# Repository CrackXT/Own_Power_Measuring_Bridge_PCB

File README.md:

# Own_Power_Measuring_Bridge_PCB

PCB files for Power Measuring Bridge 

# Description

Allows current consumption to be measured directly at the source.

The board can be produced here (AISLER) with the files (.brd and .sch) or by any other PCB manufacturer. -> https://aisler.net/

# Serie

- .dev

# Layout

Top<br>

Bottom<br>

Routing/Dimensions(inch)<br>

Schematic<br>
Schematic as .pdf at the top of the page.

# License

Open hardware, use it, mod it, whatever you want, feel free...

# Thanks!

Own design and layout.

# Version - Build

v1.0 - 06.11.2022

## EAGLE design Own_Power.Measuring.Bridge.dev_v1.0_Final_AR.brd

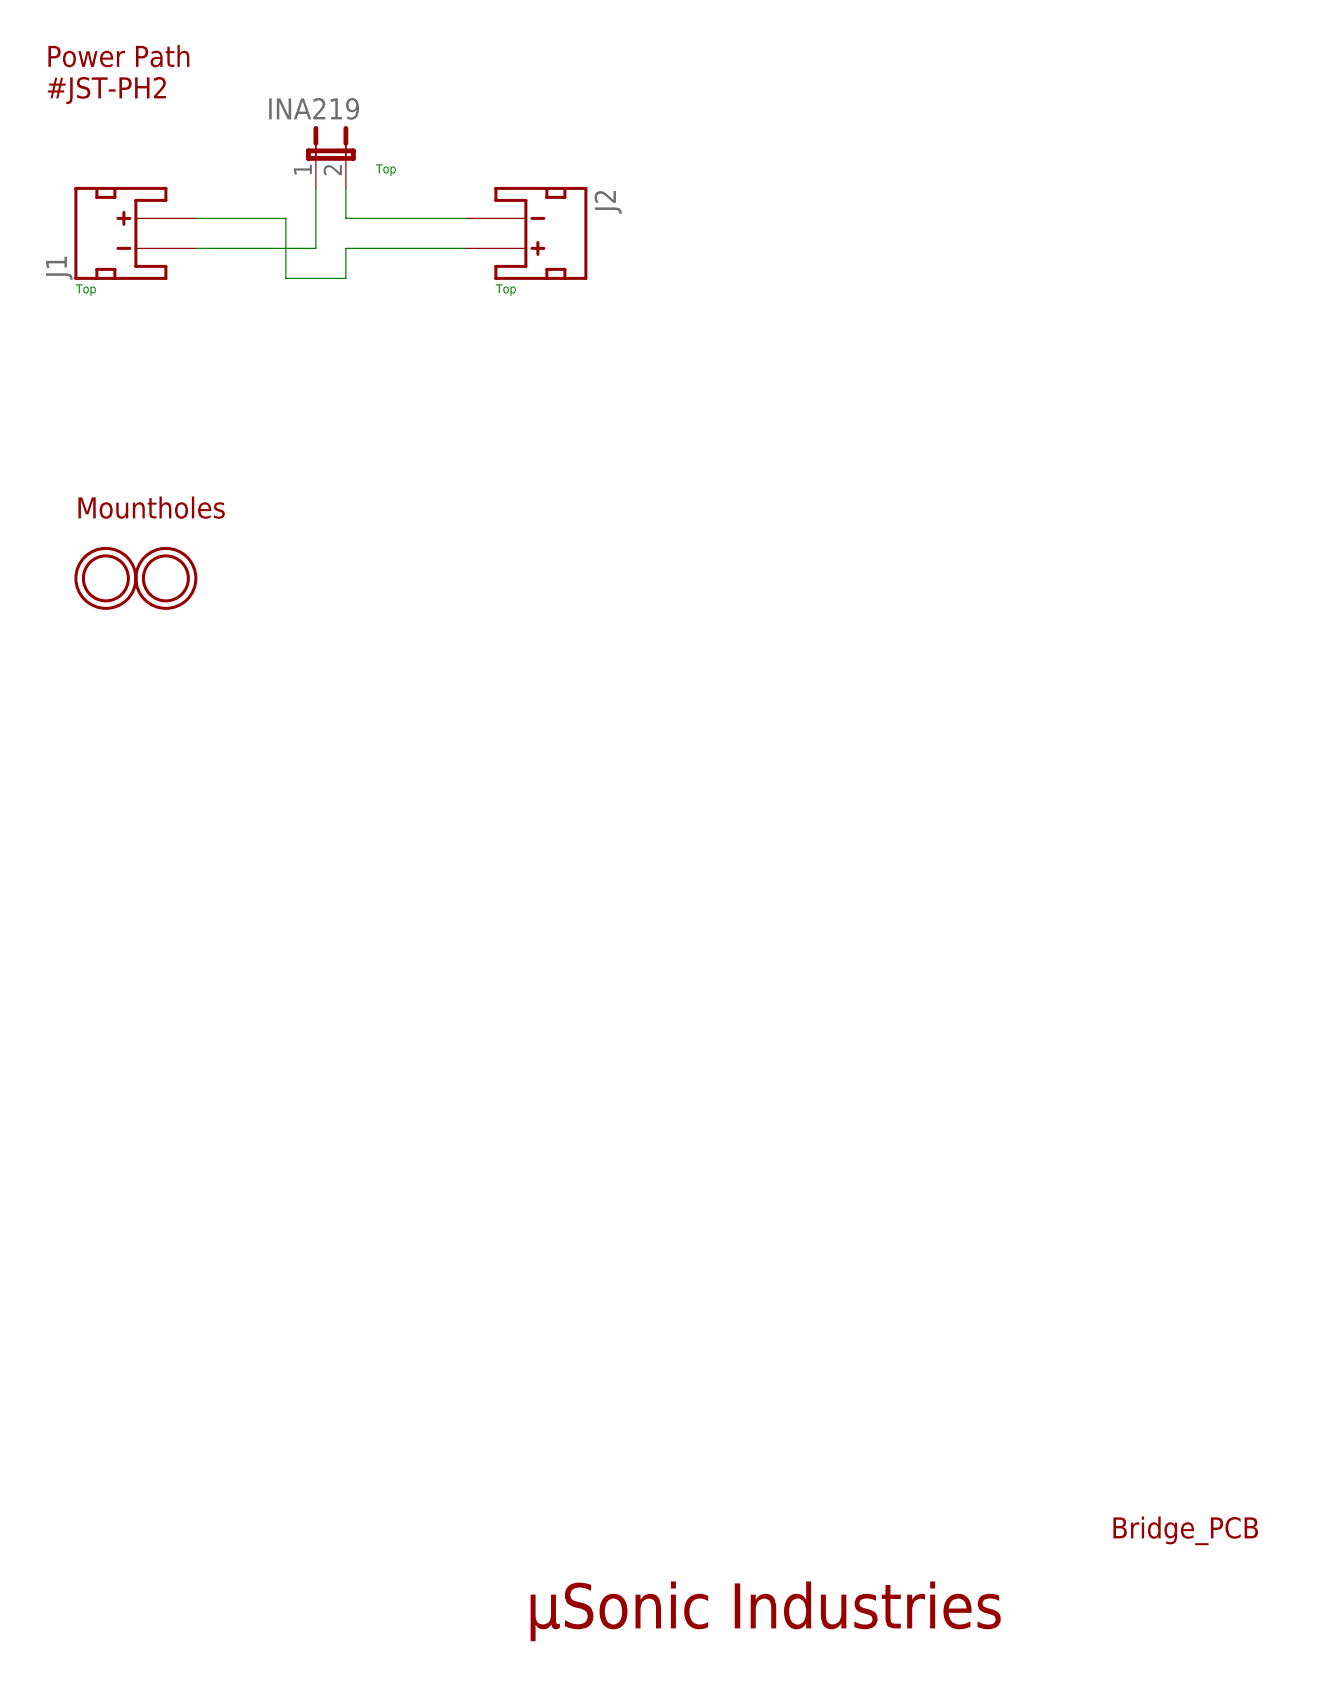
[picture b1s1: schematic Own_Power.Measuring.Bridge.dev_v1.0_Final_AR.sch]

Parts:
INA219: JP1E; JP1
J1: Input; JST-2-SMD
J2: Output; JST-2-SMD
U$18, U$19: MOUNTINGHOLE2.5; MOUNTINGHOLE_2.5_PLATED

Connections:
3V3: J1.2 (+), J2.2 (+)
GND1: INA219.1, J1.1 (-)
GND2: INA219.2, J2.1 (-)

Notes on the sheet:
µSonic Industries
Bridge_PCB
Power Path #JST-PH2
Mountholes
Top

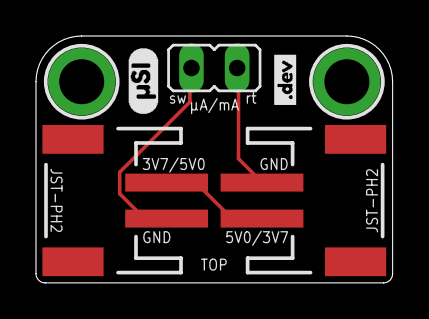
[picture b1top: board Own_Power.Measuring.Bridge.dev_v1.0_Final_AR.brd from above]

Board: 2 copper layers, 19.8 x 13.7 mm, 8 parts (1 on the bottom side), 3 nets.

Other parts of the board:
U$2: #DEV0
U$4: OSHW-LOGO-S
U$5: #SI0

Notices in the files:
parts and their libraries:
microbuilder: This work is placed in the public domain, and may be freely used for commercial and non-commercial work with the following conditions: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
SparkFun-Aesthetics: Licensing: Creative Commons ShareAlike 4.0 International - https://creativecommons.org/licenses/by-sa/4.0
